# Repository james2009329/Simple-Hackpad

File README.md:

# Simple-Hackpad
Just a simple Hackpad with 3 switches, an OLED screen, and rotary encoder. It was built as part of the [Hack Club Hackpad YSWS](https://hackpad.hackclub.com/)

**[View on Printables →](https://www.printables.com/model/1747786-simple-hackpad)**

## Features

- 3 mechanical key switches
- EC11 Rotary encoder
- 128x32 OLED display
- Seeed XIAO RP2040 microcontroller
- Made in Onshape, PCB designed in KiCad

## Case & CAD

The case is a simple two-piece print. It is a base where the PCB sits, and a top cover. Everything slides together.

Designed in Onshape.

## PCB

The PCB was designed in KiCad. Key switch footprints use MX_V2. The OLED and rotary encoder connect directly to the XIAO via I2C and GPIO.

## Firmware

This hackpad runs [KMK](https://kmkfw.io/) firmware on the XIAO RP2040.

- The 4 keys act as customizable macros
- The rotary encoder can be mapped to volume, scroll, zoom, or anything else

## Bill of Materials

| Part | Qty |
|------|-----|
| Cherry MX Switches | 3 |
| Keycaps (DSA or similar) | 3 |
| EC11 Rotary Encoder + knob | 1 |
| 0.91" 128x32 OLED Display | 1 |
| Seeed XIAO RP2040 | 1 |
| 3D Printed Case | 1 set |

## Credits

- Inspired by [Orpheuspad](https://github.com/hackclub/hackpad) and the Hack Club Hackpad YSWS
- Case designed in Onshape
- PCB designed in KiCad
- Firmware: [KMK](https://kmkfw.io/)

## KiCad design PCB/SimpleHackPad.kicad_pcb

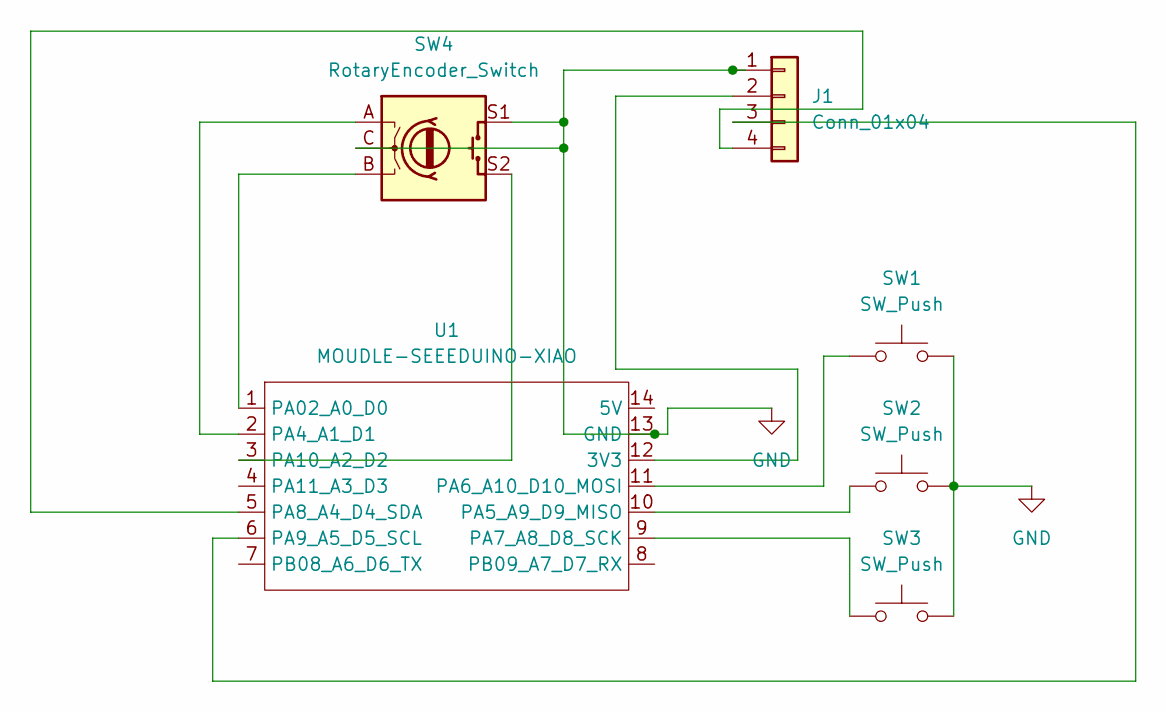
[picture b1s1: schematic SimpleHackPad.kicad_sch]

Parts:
J1: Conn_01x04; PinHeader_1x04_P2.54mm_Vertical
SW1, SW2, SW3: SW_Push; SW_Cherry_MX_1.00u_PCB
SW4: RotaryEncoder_Switch; RotaryEncoder_Alps_EC11E-Switch_Vertical_H20mm
U1: MOUDLE-SEEEDUINO-XIAO; XIAO-Generic-Hybrid-14P-2.54-21X17.8MM

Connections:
GND: J1.1, SW1.2, SW2.2, SW3.2, SW4.C, SW4.S1, U1.13 (GND)
unnamed: J1.2, U1.12 (3V3)
unnamed: J1.3, U1.6 (PA9_A5_D5_SCL)
unnamed: J1.4, U1.5 (PA8_A4_D4_SDA)
unnamed: SW4.B, U1.1 (PA02_A0_D0)
unnamed: SW4.A, U1.2 (PA4_A1_D1)
unnamed: SW2.1, U1.10 (PA5_A9_D9_MISO)
unnamed: SW1.1, U1.11 (PA6_A10_D10_MOSI)
unnamed: SW3.1, U1.9 (PA7_A8_D8_SCK)
unnamed: SW4.S2, U1.3 (PA10_A2_D2)

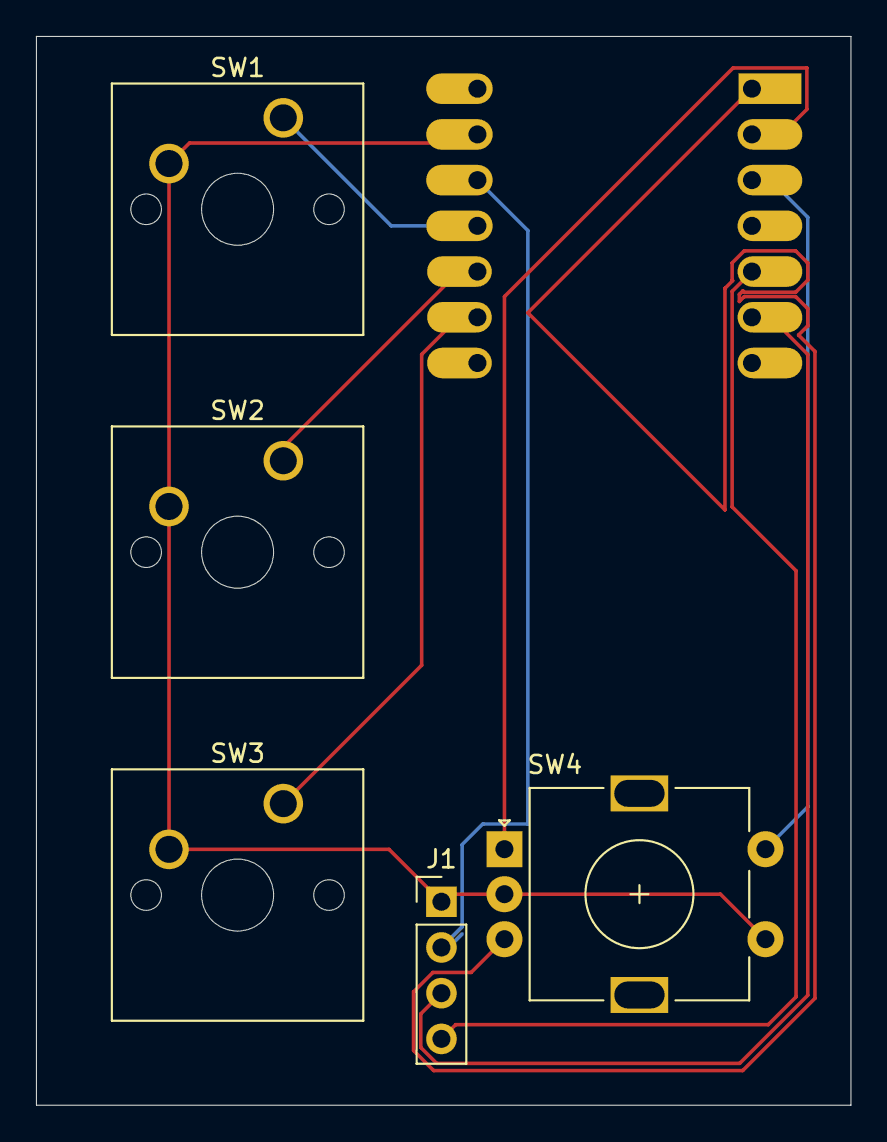
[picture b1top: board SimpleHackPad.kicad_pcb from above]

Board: 2 copper layers, 45.2 x 59.4 mm, 6 parts (1 on the bottom side), 10 nets.

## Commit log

2026-06-08 Enhance README with detailed project information
    Expanded README to include features, case design, PCB details, firmware information, and a bill of materials.
2026-06-08 Update quantities in Bill of Materials
2026-06-15 Update key switches count in README
2026-06-15 Implement keyboard shortcuts and volume control
2026-06-15 Rename firmware.uf2 to Firmware/main.pyfirmware.uf2
2026-06-15 Rename main.pyfirmware.uf2 to firmware.uf2
2026-06-15 Rename Bottom (11).step to production/Bottom.STEP
2026-06-15 Rename Top (2).step to production/Top.STEP
2026-06-15 Rename gerbers.zip to production/gerbers.zip
2026-06-15 Rename SimpleHackPad.kicad_pcb to PCB/SimpleHackPad.kicad_pcb
2026-06-15 Rename SimpleHackPad.kicad_sch to PCB/SimpleHackPad.kicad_sch
2026-06-15 Rename SimpleHackPad.kicad_pro to PCB/SimpleHackPad.kicad_pro
2026-06-15 Rename assembled-model.step to CAD/assembled-model.step
2026-06-15 Rename main.py to Firmware/main.py
